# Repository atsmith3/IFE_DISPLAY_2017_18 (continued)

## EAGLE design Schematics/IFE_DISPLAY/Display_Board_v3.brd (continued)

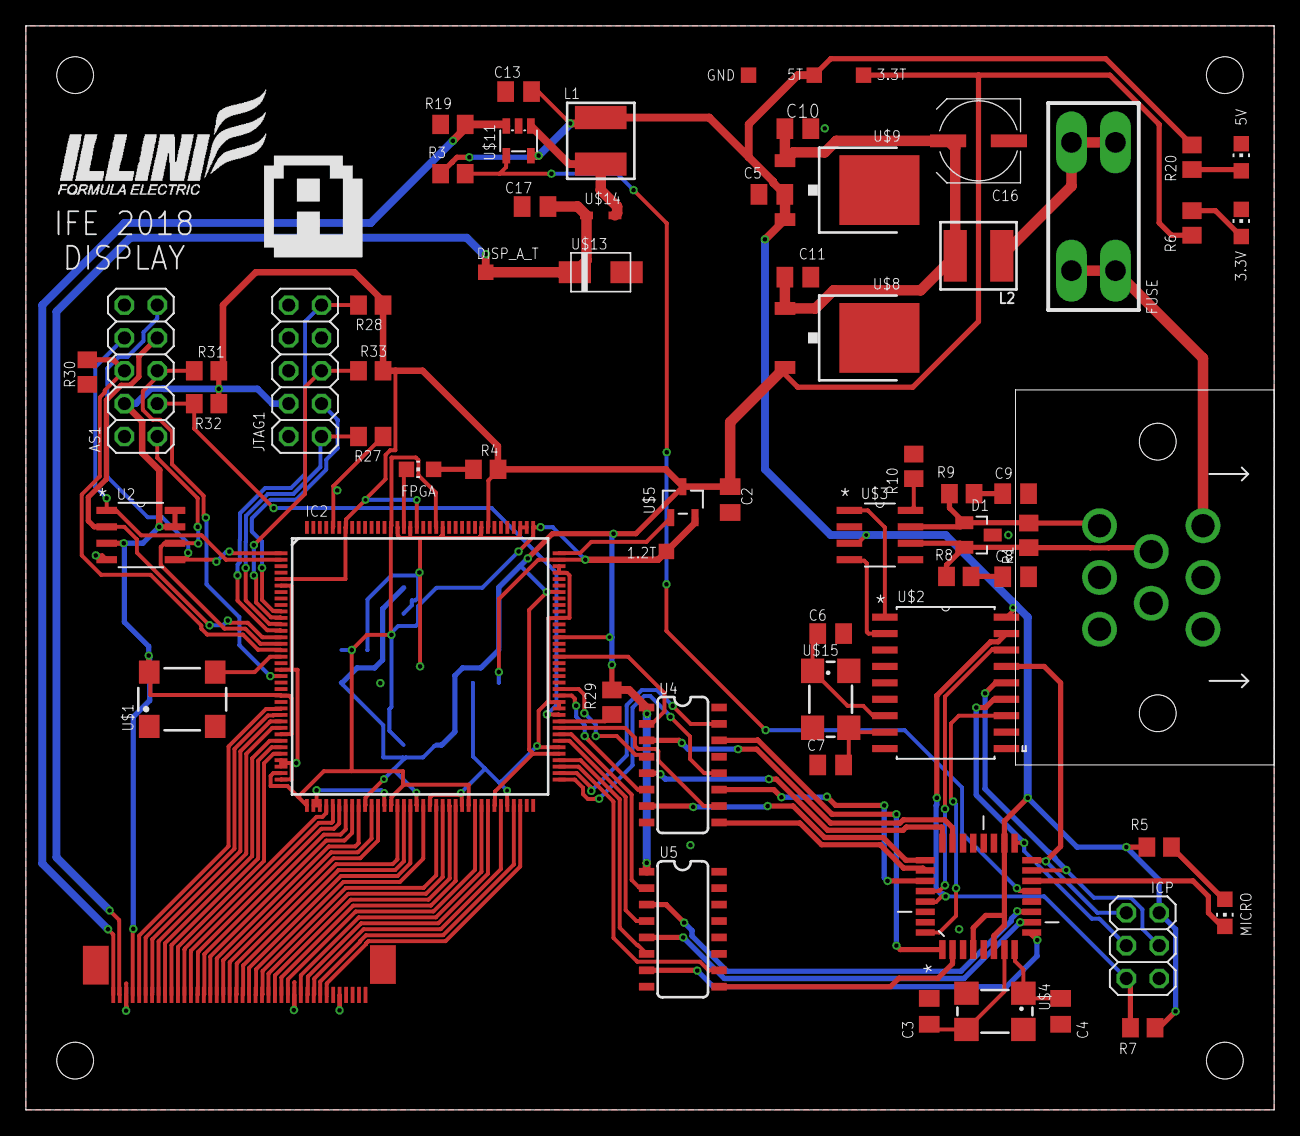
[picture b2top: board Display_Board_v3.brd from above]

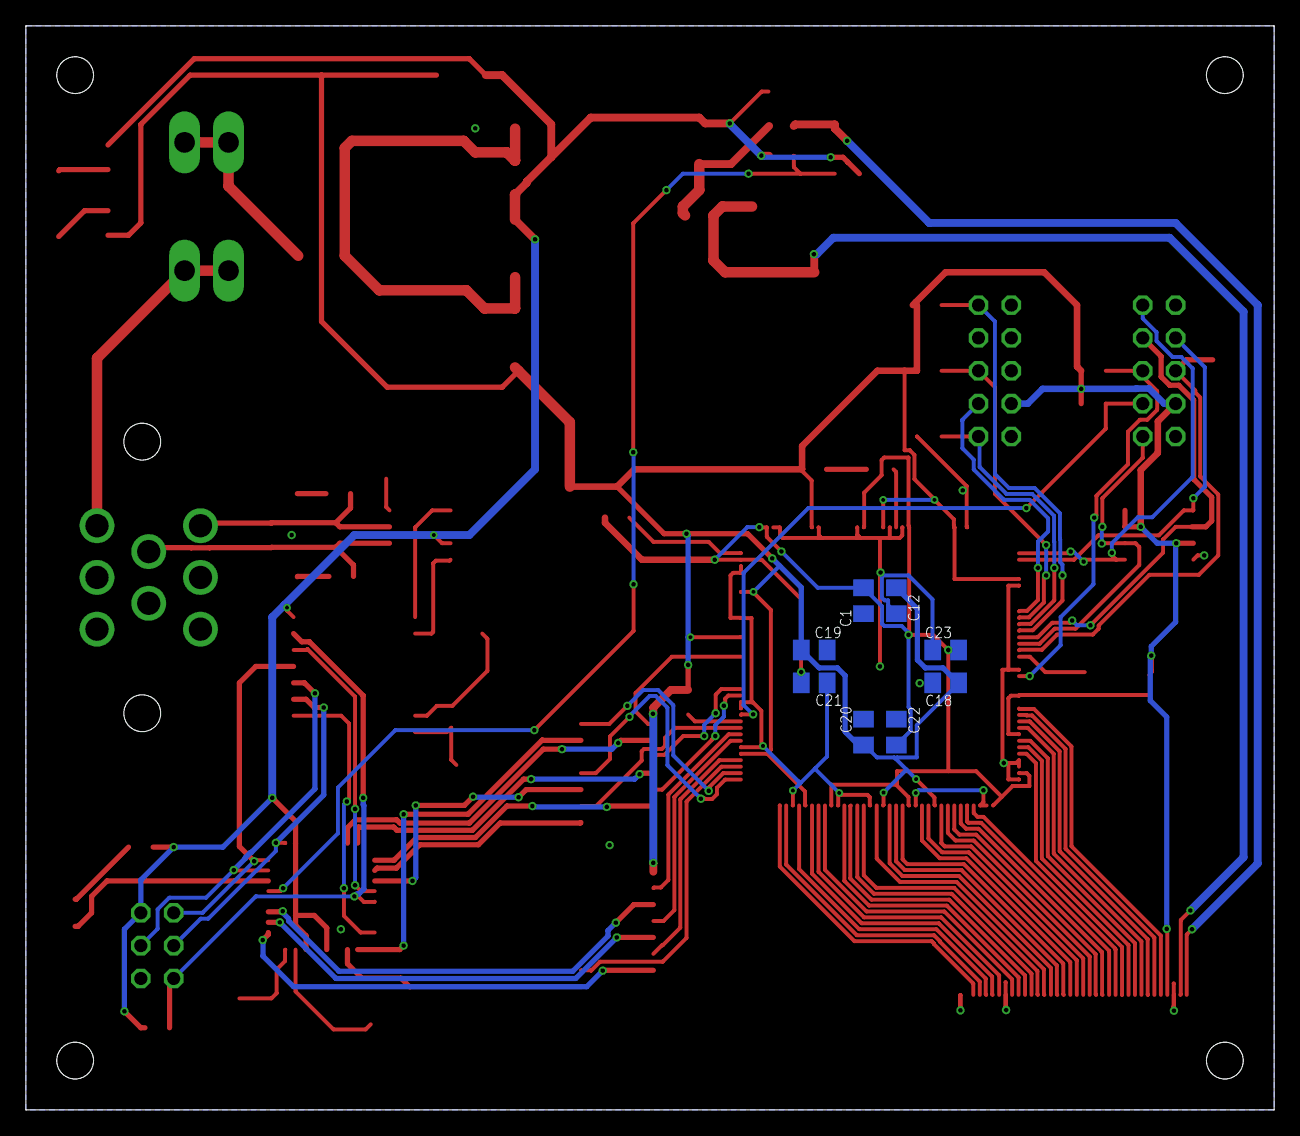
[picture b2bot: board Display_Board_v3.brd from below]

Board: 2 copper layers, 96.5 x 83.8 mm, 73 parts (8 on the bottom side), 96 nets.

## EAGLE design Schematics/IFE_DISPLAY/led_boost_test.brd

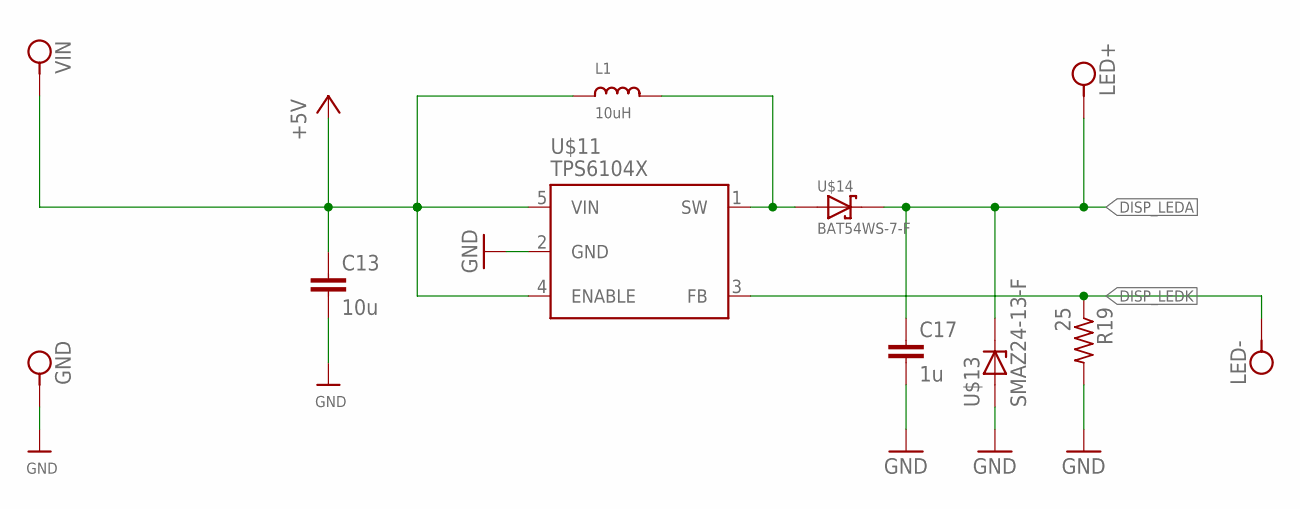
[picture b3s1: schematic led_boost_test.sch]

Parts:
C13: 10u; C0805K
C17: 1u; C0805K
GND: MOTOR_PAD
L1: 10uH; INDUCTOR_5X5MM_NR5040_NOTHERMALS
LED+: MOTOR_PAD
LED-: MOTOR_PAD
R19: 25; R0805
U$11: TPS6104X; SOT23-5L
U$13: SMAZ24-13-F; SMA_DIODE
U$14: BAT54WS-7-F; SOD323
VIN: MOTOR_PAD

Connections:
+5V: C13.1, L1.P$1 (1), U$11.4 (ENABLE), U$11.5 (VIN), VIN.P$1
DISP_LEDA: C17.1, LED+.P$1, U$13.C, U$14.1 (C)
DISP_LEDK: LED-.P$1, R19.1, U$11.3 (FB)
GND: C13.2, C17.2, GND.P$1, R19.2, U$11.2 (GND), U$13.A
unnamed: L1.P$2 (2), U$11.1 (SW), U$14.2 (A)

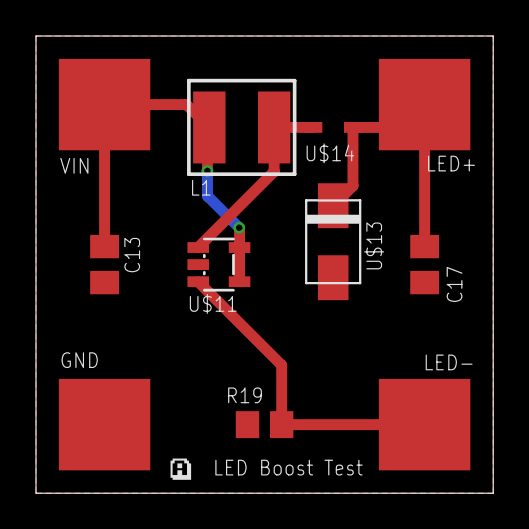
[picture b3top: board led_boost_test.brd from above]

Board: 2 copper layers, 25.4 x 25.4 mm, 11 parts (0 on the bottom side), 5 nets.

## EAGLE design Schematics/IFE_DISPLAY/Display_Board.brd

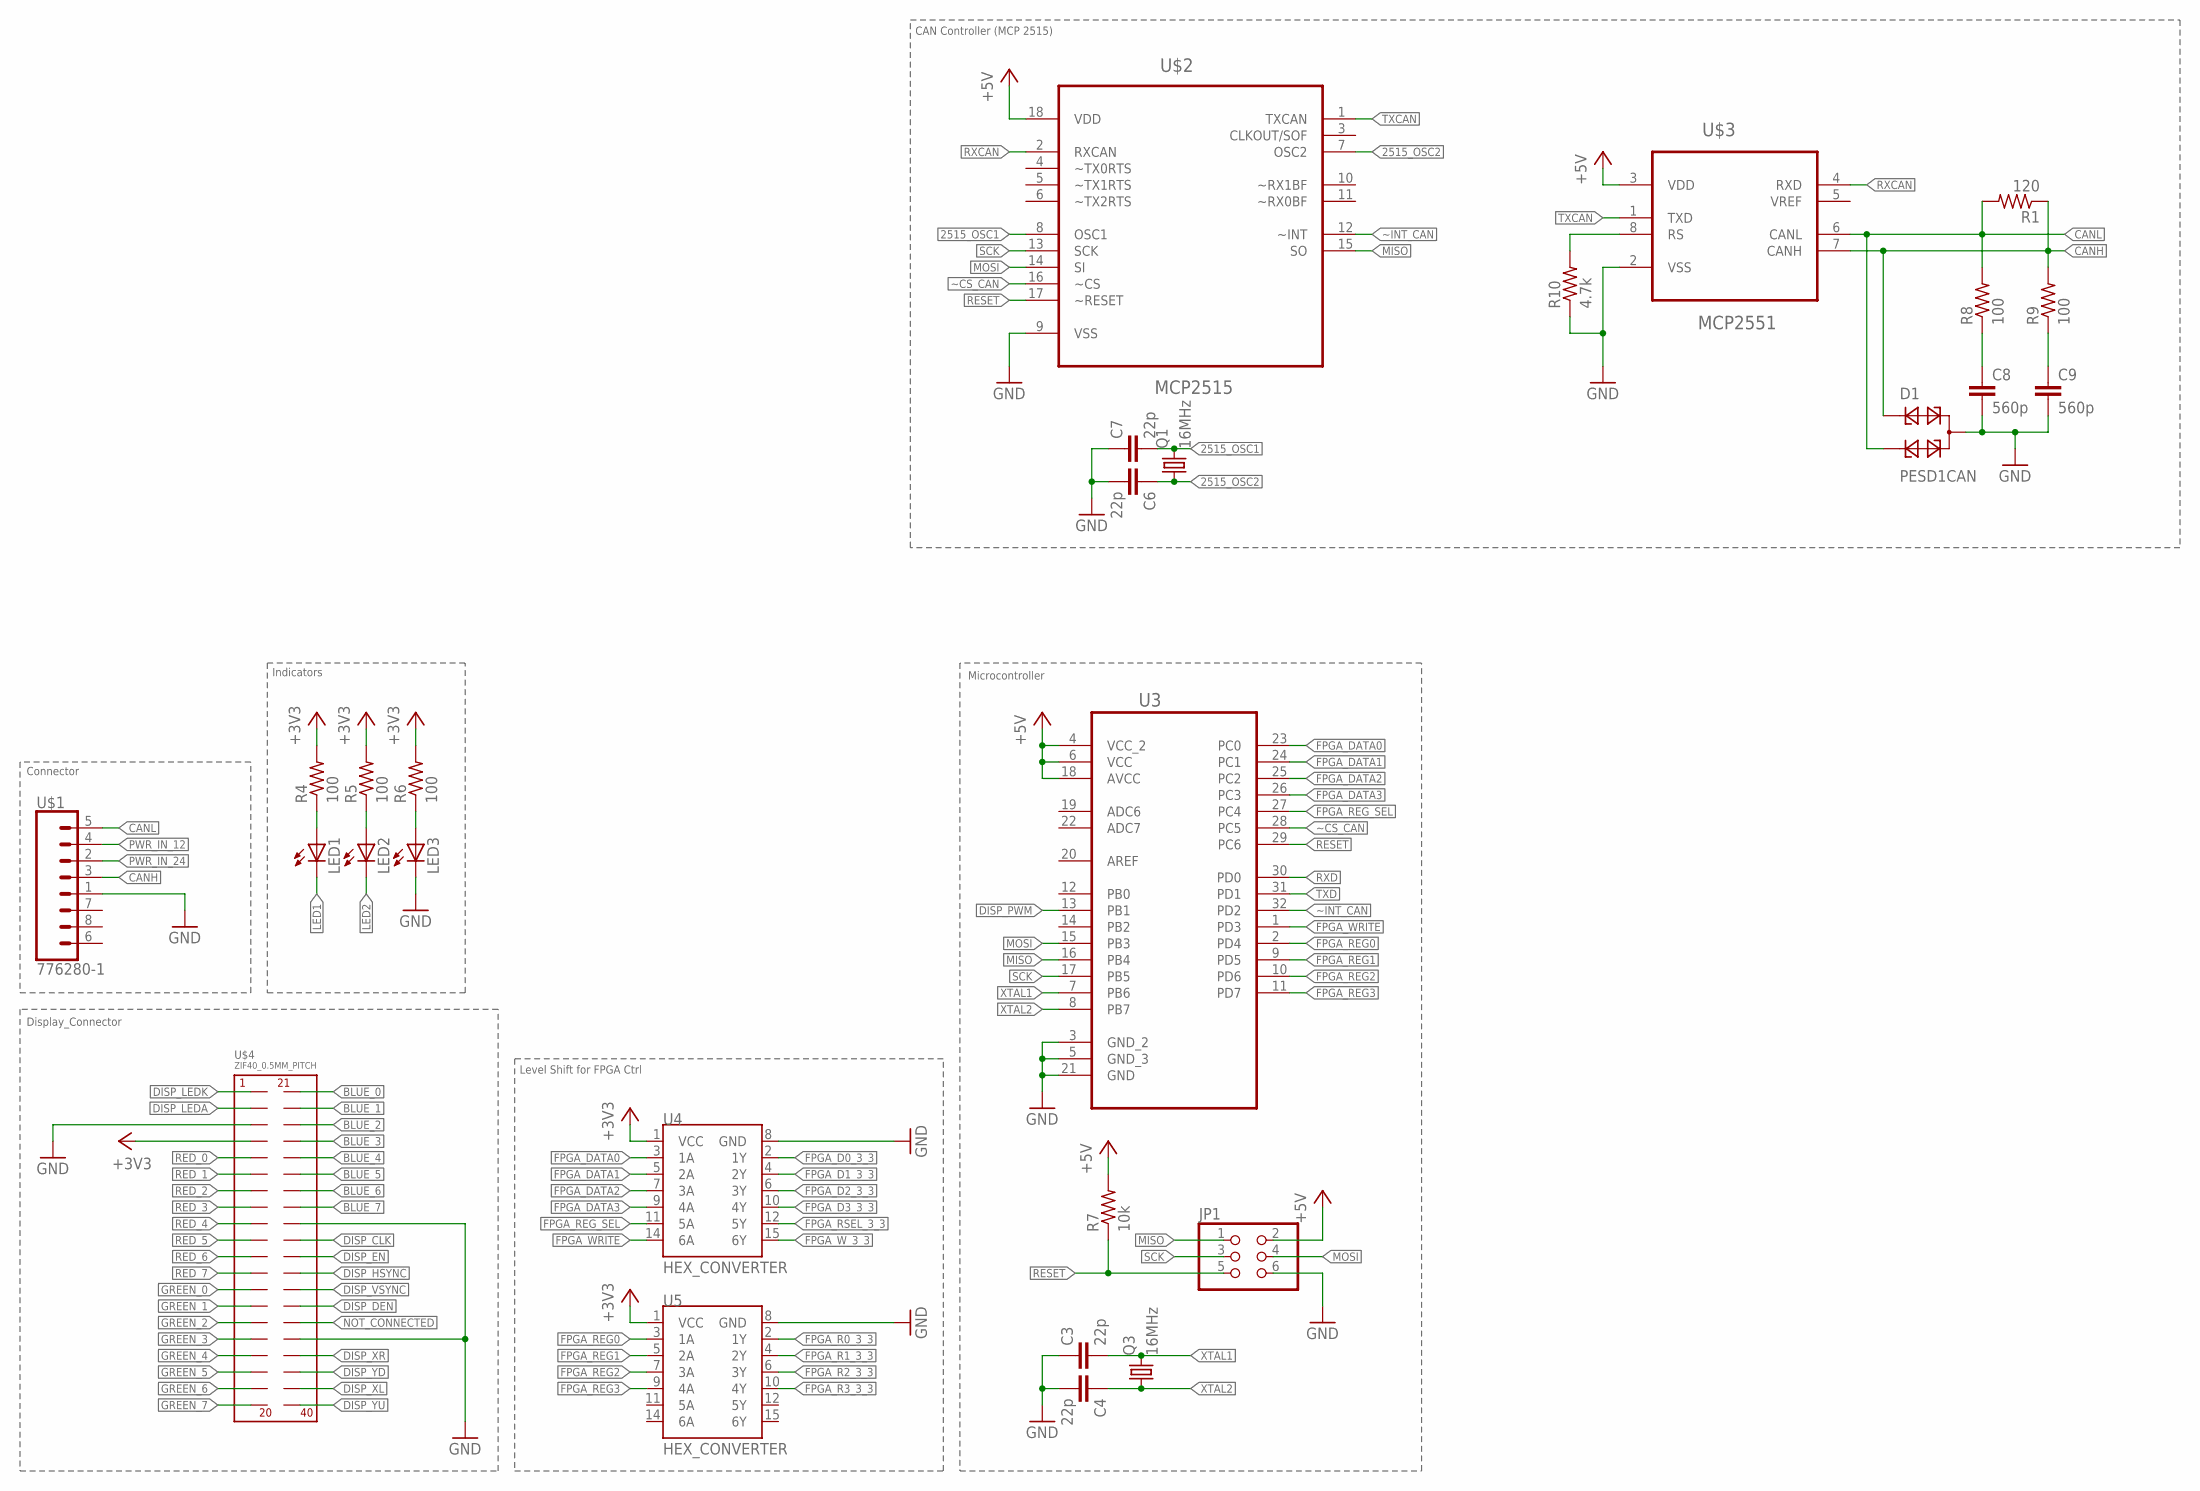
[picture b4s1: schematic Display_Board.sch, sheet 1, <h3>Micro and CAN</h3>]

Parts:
C3, C4, C6, C7: 22p; C0805K
C8, C9: 560p; C0805K
D1: PESD1CAN; SOT23
JP1: PINHD-2X3; 2X03
LED1, LED2, LED3: LEDCHIP-LED0805; CHIP-LED0805
Q1, Q3: 16MHz; CTS406
R1: 120; R0805
R4, R5, R6, R8, R9: 100; R0805
R7: 10k; R0805
R10: 4.7k; R0805
U3: ATMEGA328P-AU; QFP80P900X900X120-32N
U4, U5: HEX_CONVERTER; SO016
U$1: 776280-1
U$2: MCP2515; SOIC127P1034X264-18N
U$3: MCP2551; SOIC127P600X175-8N
U$4: ZIF40_0.5MM_PITCH; ZIF40

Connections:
2515_OSC1: C7.2, Q1.3 (2), U$2.8 (OSC1)
2515_OSC2: C6.1, Q1.1, U$2.7 (OSC2)
+3V3: R4.2, R5.2, R6.2, U4.1 (VCC), U5.1 (VCC), U$4.P$4; also elsewhere on the board
+5V: JP1.2, R7.2, U3.4 (VCC_2), U3.6 (VCC), U3.18 (AVCC), U$2.18 (VDD), U$3.3 (VDD); also elsewhere on the board
BLUE_0: U$4.P$21; also elsewhere on the board
BLUE_1: U$4.P$22; also elsewhere on the board
BLUE_2: U$4.P$23; also elsewhere on the board
BLUE_3: U$4.P$24; also elsewhere on the board
BLUE_4: U$4.P$25; also elsewhere on the board
BLUE_5: U$4.P$26; also elsewhere on the board
BLUE_6: U$4.P$27; also elsewhere on the board
BLUE_7: U$4.P$28; also elsewhere on the board
CANH: D1.1, R1.1, R9.2, U$1.3 (5), U$3.7 (CANH)
CANL: D1.2, R1.2, R8.2, U$1.5 (8), U$3.6 (CANL)
DISP_CLK: U$4.P$30; also elsewhere on the board
DISP_DEN: U$4.P$34; also elsewhere on the board
DISP_EN: U$4.P$31; also elsewhere on the board
DISP_HSYNC: U$4.P$32; also elsewhere on the board
DISP_LEDA: U$4.P$2; also elsewhere on the board
DISP_LEDK: U$4.P$1; also elsewhere on the board
DISP_PWM: U3.13 (PB1); also elsewhere on the board
DISP_VSYNC: U$4.P$33; also elsewhere on the board
DISP_XL: U$4.P$39
DISP_XR: U$4.P$37
DISP_YD: U$4.P$38
DISP_YU: U$4.P$40
FPGA_D0_3_3: U4.2 (1Y); also elsewhere on the board
FPGA_D1_3_3: U4.4 (2Y); also elsewhere on the board
FPGA_D2_3_3: U4.6 (3Y); also elsewhere on the board
FPGA_D3_3_3: U4.10 (4Y); also elsewhere on the board
FPGA_DATA0: U3.23 (PC0), U4.3 (1A)
FPGA_DATA1: U3.24 (PC1), U4.5 (2A)
FPGA_DATA2: U3.25 (PC2), U4.7 (3A)
FPGA_DATA3: U3.26 (PC3), U4.9 (4A)
FPGA_R0_3_3: U5.2 (1Y); also elsewhere on the board
FPGA_R1_3_3: U5.4 (2Y); also elsewhere on the board
FPGA_R2_3_3: U5.6 (3Y); also elsewhere on the board
FPGA_R3_3_3: U5.10 (4Y); also elsewhere on the board
FPGA_REG0: U3.2 (PD4), U5.3 (1A)
FPGA_REG1: U3.9 (PD5), U5.5 (2A)
FPGA_REG2: U3.10 (PD6), U5.7 (3A)
FPGA_REG3: U3.11 (PD7), U5.9 (4A)
FPGA_REG_SEL: U3.27 (PC4), U4.11 (5A)
FPGA_RSEL_3_3: U4.12 (5Y); also elsewhere on the board
FPGA_WRITE: U3.1 (PD3), U4.14 (6A)
FPGA_W_3_3: U4.15 (6Y); also elsewhere on the board
GND: C3.1, C4.2, C6.2, C7.1, C8.2, C9.2, D1.3, JP1.6, LED3.C, R10.1, U3.3 (GND_2), U3.5 (GND_3), U3.21 (GND), U4.8 (GND), U5.8 (GND), U$1.1 (4), U$2.9 (VSS), U$3.2 (VSS), U$4.P$3, U$4.P$29, U$4.P$36; also elsewhere on the board
GREEN_0: U$4.P$13; also elsewhere on the board
GREEN_1: U$4.P$14; also elsewhere on the board
GREEN_2: U$4.P$15; also elsewhere on the board
GREEN_3: U$4.P$16; also elsewhere on the board
GREEN_4: U$4.P$17; also elsewhere on the board
GREEN_5: U$4.P$18; also elsewhere on the board
GREEN_6: U$4.P$19; also elsewhere on the board
GREEN_7: U$4.P$20; also elsewhere on the board
LED1: LED1.C; also elsewhere on the board
LED2: LED2.C; also elsewhere on the board
MISO: JP1.1, U3.16 (PB4), U$2.15 (SO)
MOSI: JP1.4, U3.15 (PB3), U$2.14 (SI)
unnamed: LED1.A, R4.1
unnamed: LED2.A, R5.1
unnamed: LED3.A, R6.1
unnamed: R10.2, U$3.8 (RS)
unnamed: C8.1, R8.1
unnamed: C9.1, R9.1
NOT_CONNECTED: U$4.P$35
PWR_IN_12: U$1.4 (7); also elsewhere on the board
PWR_IN_24: U$1.2 (6)
RED_0: U$4.P$5; also elsewhere on the board
RED_1: U$4.P$6; also elsewhere on the board
RED_2: U$4.P$7; also elsewhere on the board
RED_3: U$4.P$8; also elsewhere on the board
RED_4: U$4.P$9; also elsewhere on the board
RED_5: U$4.P$10; also elsewhere on the board
RED_6: U$4.P$11; also elsewhere on the board
RED_7: U$4.P$12; also elsewhere on the board
RESET: JP1.5, R7.1, U3.29 (PC6), U$2.17 (~RESET)
RXCAN: U$2.2 (RXCAN), U$3.4 (RXD)
RXD: U3.30 (PD0)
SCK: JP1.3, U3.17 (PB5), U$2.13 (SCK)
TXCAN: U$2.1 (TXCAN), U$3.1 (TXD)
TXD: U3.31 (PD1)
XTAL1: C3.2, Q3.3 (2), U3.7 (PB6)
XTAL2: C4.1, Q3.1, U3.8 (PB7)
~CS_CAN: U3.28 (PC5), U$2.16 (~CS)
~INT_CAN: U3.32 (PD2), U$2.12 (~INT)

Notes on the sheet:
Microcontroller
CAN Controller (MCP 2515)
Indicators
Level Shift for FPGA Ctrl
Connector
Display_Connector

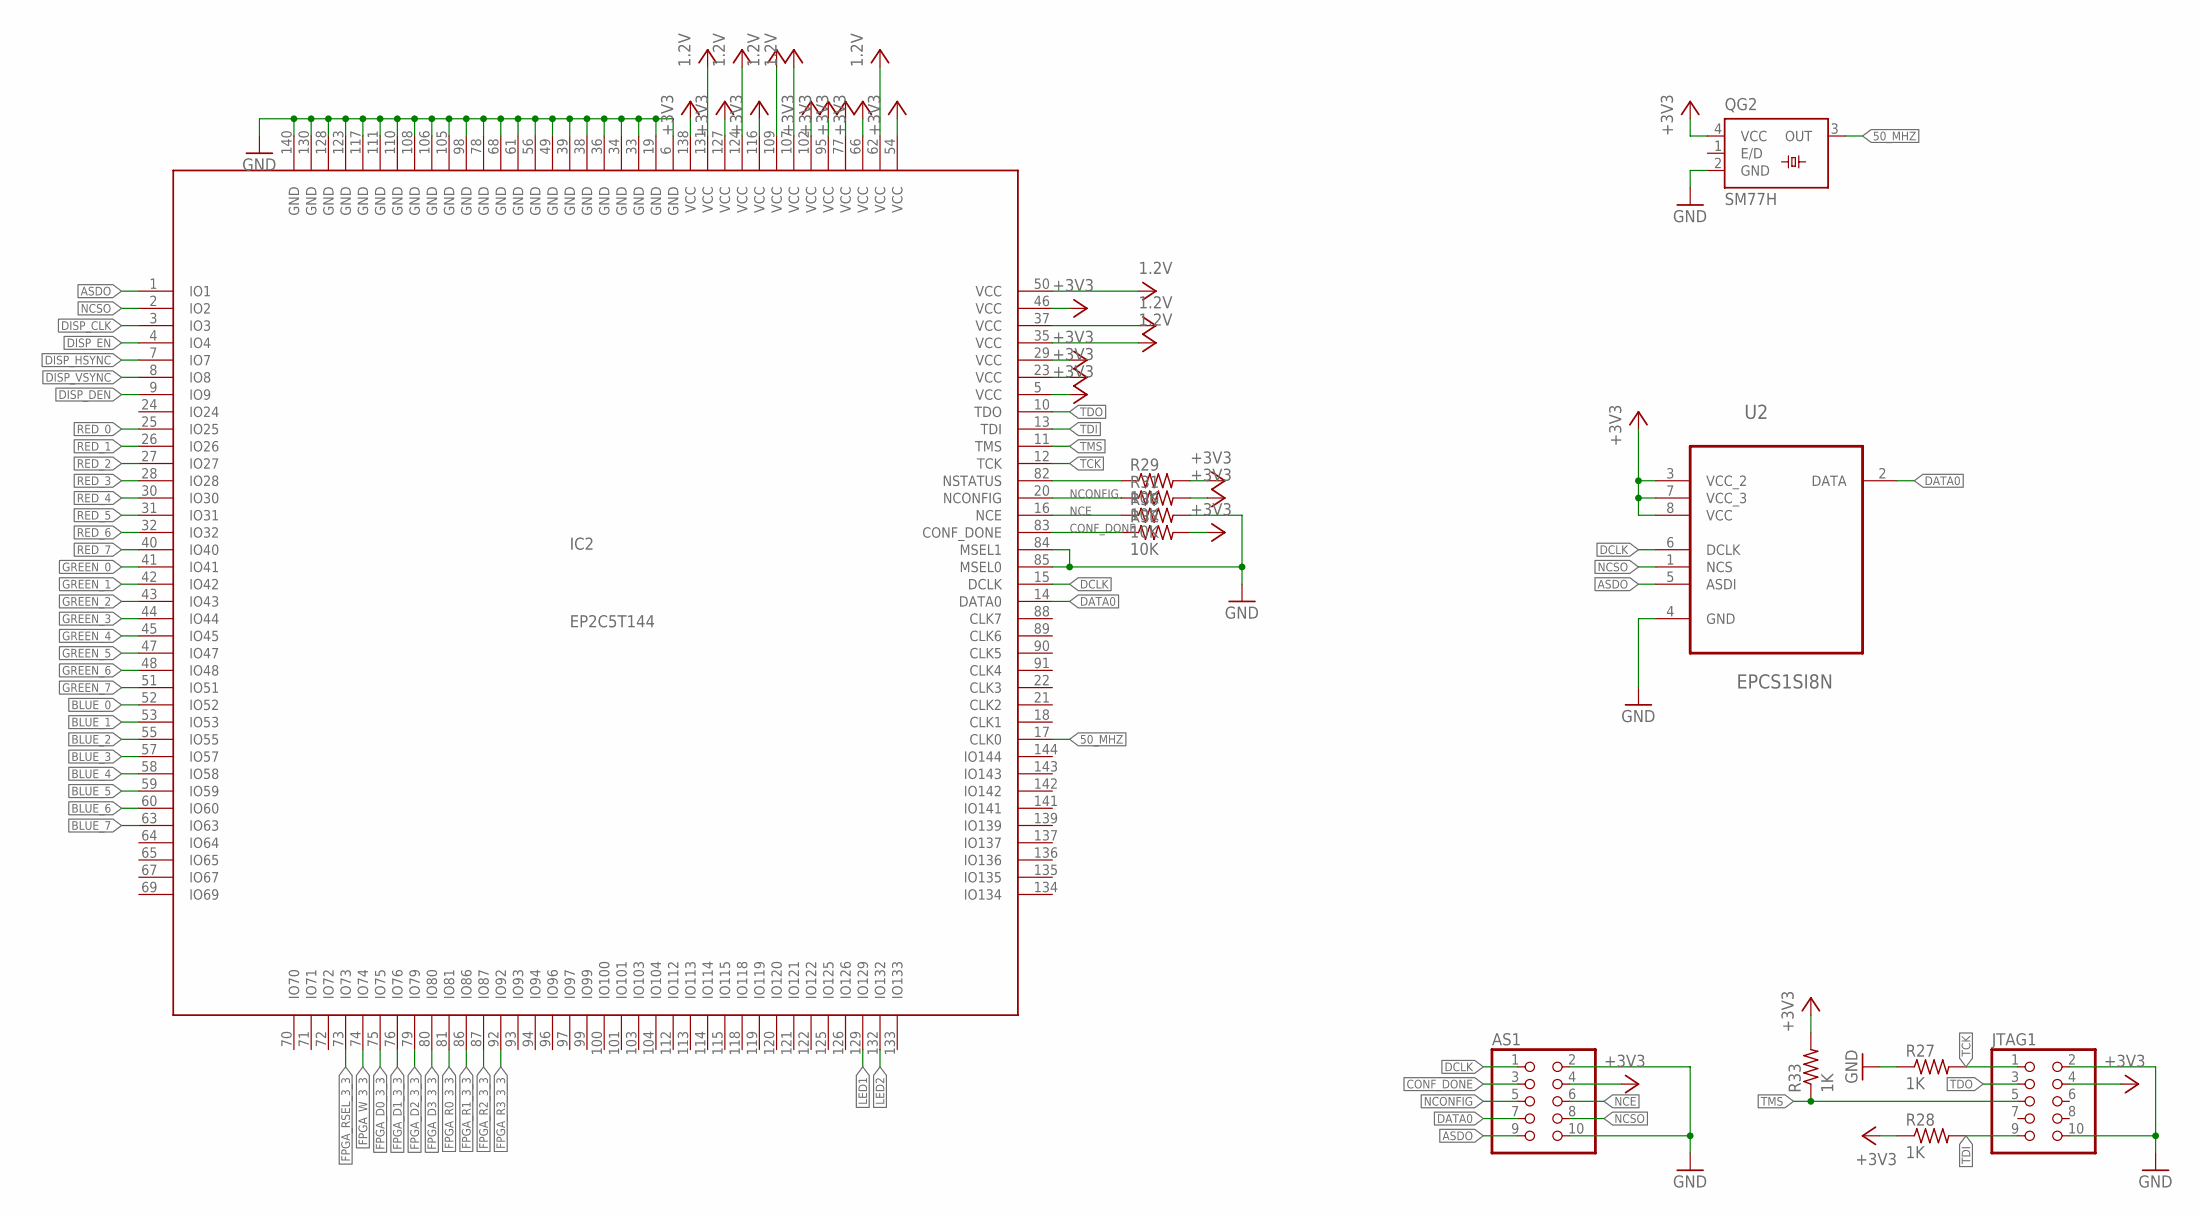
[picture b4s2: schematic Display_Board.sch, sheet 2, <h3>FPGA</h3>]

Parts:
AS1: PINHD-2X5; 2X05
IC2: EP2C5T144; TQFP144
JTAG1: PINHD-2X5; 2X05
QG2: SM77H
R27, R28, R33: 1K; R0805
R29, R30, R31, R32: 10K; R0805
U2: EPCS1SI8N; SOIC127P600X175-8N

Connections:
50_MHZ: IC2.17 (CLK0), QG2.3 (OUT)
+3V3: AS1.4, IC2.5 (VCC), IC2.23 (VCC), IC2.29 (VCC), IC2.46 (VCC), IC2.54 (VCC), IC2.66 (VCC), IC2.77 (VCC), IC2.95 (VCC), IC2.102 (VCC), IC2.116 (VCC), IC2.127 (VCC), IC2.138 (VCC), JTAG1.4, QG2.4 (VCC), R28.1, R29.2, R31.2, R32.2, R33.2, U2.3 (VCC_2), U2.7 (VCC_3), U2.8 (VCC); also elsewhere on the board
ASDO: AS1.9, IC2.1 (IO1), U2.5 (ASDI)
BLUE_0: IC2.52 (IO52); also elsewhere on the board
BLUE_1: IC2.53 (IO53); also elsewhere on the board
BLUE_2: IC2.55 (IO55); also elsewhere on the board
BLUE_3: IC2.57 (IO57); also elsewhere on the board
BLUE_4: IC2.58 (IO58); also elsewhere on the board
BLUE_5: IC2.59 (IO59); also elsewhere on the board
BLUE_6: IC2.60 (IO60); also elsewhere on the board
BLUE_7: IC2.63 (IO63); also elsewhere on the board
CONF_DONE: AS1.3, IC2.83 (CONF_DONE), R32.1
DATA0: AS1.7, IC2.14 (DATA0), U2.2 (DATA)
DCLK: AS1.1, IC2.15 (DCLK), U2.6 (DCLK)
DISP_CLK: IC2.3 (IO3); also elsewhere on the board
DISP_DEN: IC2.9 (IO9); also elsewhere on the board
DISP_EN: IC2.4 (IO4); also elsewhere on the board
DISP_HSYNC: IC2.7 (IO7); also elsewhere on the board
DISP_VSYNC: IC2.8 (IO8); also elsewhere on the board
FPGA_D0_3_3: IC2.75 (IO75); also elsewhere on the board
FPGA_D1_3_3: IC2.76 (IO76); also elsewhere on the board
FPGA_D2_3_3: IC2.79 (IO79); also elsewhere on the board
FPGA_D3_3_3: IC2.80 (IO80); also elsewhere on the board
FPGA_R0_3_3: IC2.81 (IO81); also elsewhere on the board
FPGA_R1_3_3: IC2.86 (IO86); also elsewhere on the board
FPGA_R2_3_3: IC2.87 (IO87); also elsewhere on the board
FPGA_R3_3_3: IC2.92 (IO92); also elsewhere on the board
FPGA_RSEL_3_3: IC2.73 (IO73); also elsewhere on the board
FPGA_W_3_3: IC2.74 (IO74); also elsewhere on the board
GND: AS1.2, AS1.10, IC2.6 (GND), IC2.19 (GND), IC2.33 (GND), IC2.34 (GND), IC2.36 (GND), IC2.38 (GND), IC2.39 (GND), IC2.49 (GND), IC2.56 (GND), IC2.61 (GND), IC2.68 (GND), IC2.78 (GND), IC2.84 (MSEL1), IC2.85 (MSEL0), IC2.98 (GND), IC2.105 (GND), IC2.106 (GND), IC2.108 (GND), IC2.110 (GND), IC2.111 (GND), IC2.117 (GND), IC2.123 (GND), IC2.128 (GND), IC2.130 (GND), IC2.140 (GND), JTAG1.2, JTAG1.10, QG2.2 (GND), R27.1, R30.2, U2.4 (GND); also elsewhere on the board
GREEN_0: IC2.41 (IO41); also elsewhere on the board
GREEN_1: IC2.42 (IO42); also elsewhere on the board
GREEN_2: IC2.43 (IO43); also elsewhere on the board
GREEN_3: IC2.44 (IO44); also elsewhere on the board
GREEN_4: IC2.45 (IO45); also elsewhere on the board
GREEN_5: IC2.47 (IO47); also elsewhere on the board
GREEN_6: IC2.48 (IO48); also elsewhere on the board
GREEN_7: IC2.51 (IO51); also elsewhere on the board
LED1: IC2.129 (IO129); also elsewhere on the board
LED2: IC2.132 (IO132); also elsewhere on the board
unnamed: IC2.82 (NSTATUS), R29.1
NCE: AS1.6, IC2.16 (NCE), R30.1
NCONFIG: AS1.5, IC2.20 (NCONFIG), R31.1
NCSO: AS1.8, IC2.2 (IO2), U2.1 (NCS)
RED_0: IC2.25 (IO25); also elsewhere on the board
RED_1: IC2.26 (IO26); also elsewhere on the board
RED_2: IC2.27 (IO27); also elsewhere on the board
RED_3: IC2.28 (IO28); also elsewhere on the board
RED_4: IC2.30 (IO30); also elsewhere on the board
RED_5: IC2.31 (IO31); also elsewhere on the board
RED_6: IC2.32 (IO32); also elsewhere on the board
RED_7: IC2.40 (IO40); also elsewhere on the board
TCK: IC2.12 (TCK), JTAG1.1, R27.2
TDI: IC2.13 (TDI), JTAG1.9, R28.2
TDO: IC2.10 (TDO), JTAG1.3
TMS: IC2.11 (TMS), JTAG1.5, R33.1
VCC: IC2.35 (VCC), IC2.37 (VCC), IC2.50 (VCC), IC2.62 (VCC), IC2.107 (VCC), IC2.109 (VCC), IC2.124 (VCC), IC2.131 (VCC); also elsewhere on the board

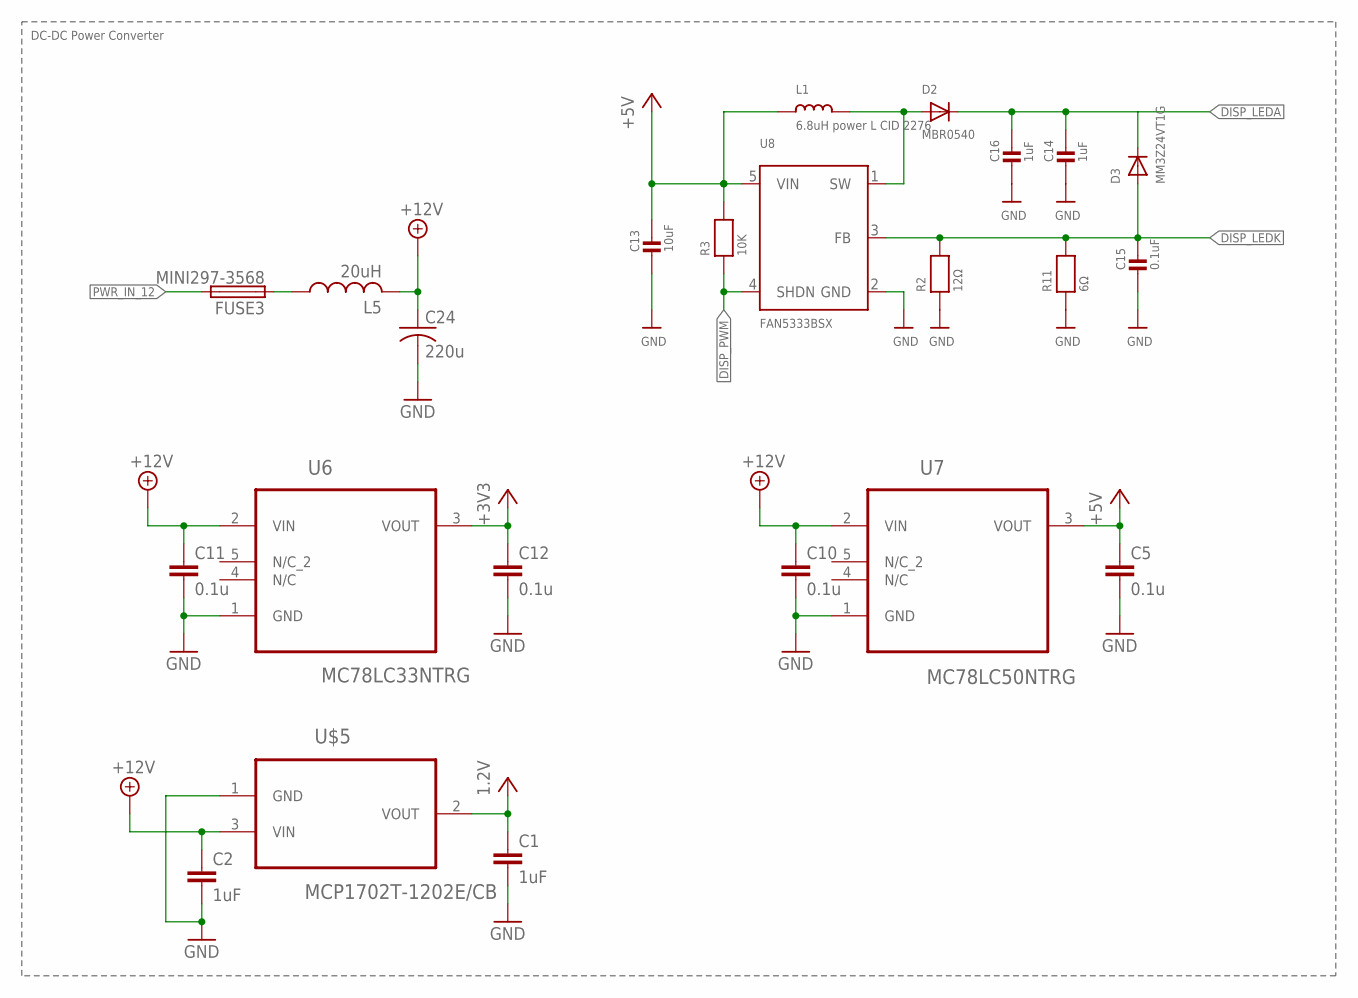
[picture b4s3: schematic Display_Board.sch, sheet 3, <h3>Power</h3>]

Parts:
C1, C2: 1uF; C0805K
C5, C10, C11, C12: 0.1u; C0805K
C13: 10uF; _0805MP
C14, C16: 1uF; _0805MP
C15: 0.1uF; _0805MP
C24: 220u; C1206
D2: MBR0540; SOD-123
D3: MM3Z24VT1G; SMADIODE
FUSE3: MINI297-3568; 3568
L1: 6.8uH power L CID 2276; INDUCTOR_5X5MM_NR5040_NOTHERMALS
L5: 20uH; MSS7348
R2: 12Ω; _0805MP
R3: 10K; _0805MP
R11: 6Ω; _0805MP
U6: MC78LC33NTRG; SOT95P275X110-5N
U7: MC78LC50NTRG; SOT95P275X110-5N
U8: FAN5333BSX; SOT23-5@1
U$5: MCP1702T-1202E/CB; SOT95P300X145-3N

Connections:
+3V3: C12.1, U6.3 (VOUT); also elsewhere on the board
+5V: C5.1, C13.1, L1.P$1 (1), R3.2, U7.3 (VOUT), U8.5 (VIN); also elsewhere on the board
+12V: C2.1, C10.1, C11.1, C24.1, L5.P$2 (2), U6.2 (VIN), U7.2 (VIN), U$5.3 (VIN)
DISP_LEDA: C14.1, C16.1, D2.C, D3.C; also elsewhere on the board
DISP_LEDK: C15.1, D3.A, R2.2, R11.2, U8.3 (FB); also elsewhere on the board
DISP_PWM: R3.1, U8.4 (SHDN); also elsewhere on the board
GND: C1.2, C2.2, C5.2, C10.2, C11.2, C12.2, C13.2, C14.2, C15.2, C16.2, C24.2, R2.1, R11.1, U6.1 (GND), U7.1 (GND), U8.2 (GND), U$5.1 (GND); also elsewhere on the board
unnamed: FUSE3.P$1 (1), FUSE3.P$4 (1), L5.P$1 (1)
unnamed: D2.A, L1.P$2 (2), U8.1 (SW)
PWR_IN_12: FUSE3.P$2 (2), FUSE3.P$3 (2); also elsewhere on the board
VCC: C1.1, U$5.2 (VOUT); also elsewhere on the board

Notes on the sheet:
DC-DC Power Converter

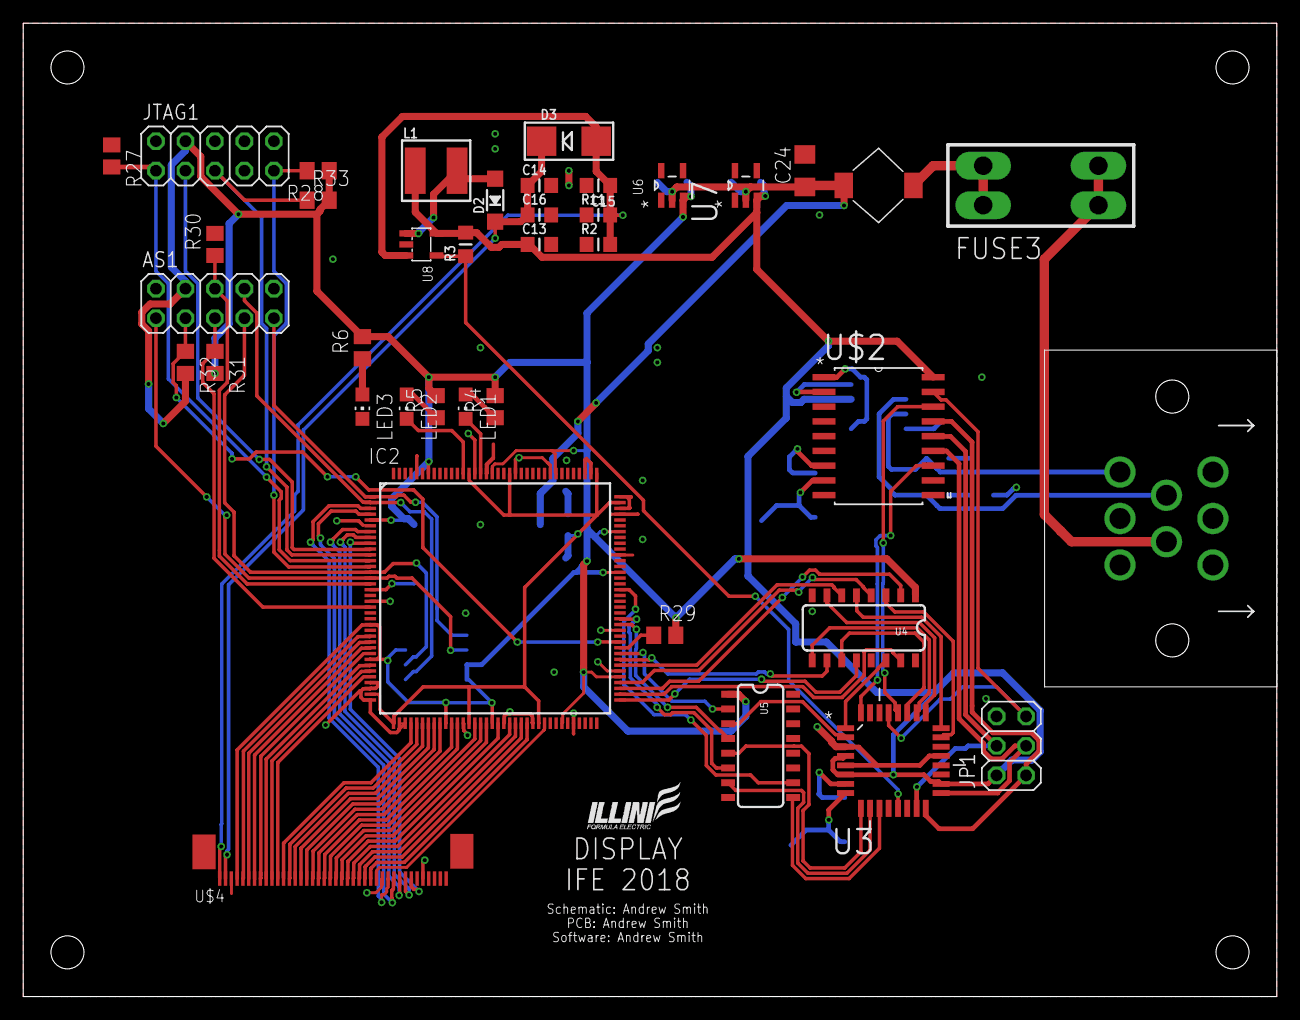
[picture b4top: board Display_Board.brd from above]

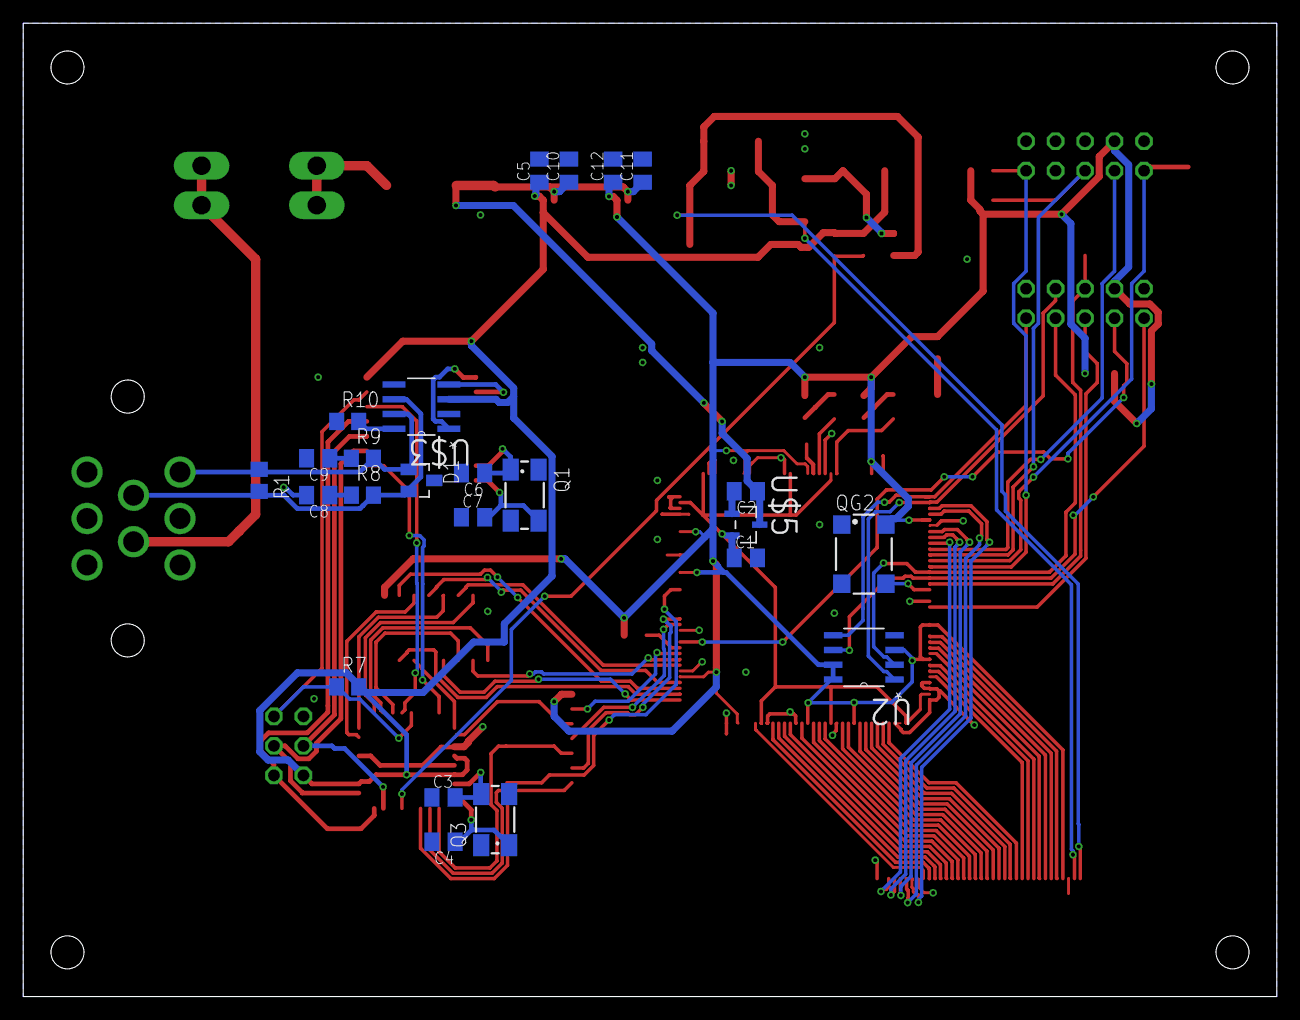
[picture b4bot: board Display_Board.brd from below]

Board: 2 copper layers, 108.0 x 83.8 mm, 63 parts (24 on the bottom side), 95 nets.

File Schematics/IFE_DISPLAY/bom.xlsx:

Part | Value | Device | Package | Description | MPN | Quantity | Price | Link
R11 | 6 | RESISTOR_0805MP | _0805MP | Resistors |  | 1
R2 | 12 | RESISTOR_0805MP | _0805MP | Resistors |  | 1
AS1 |  | PINHD-2X5 | 2X05 | PIN HEADER |  | 1
JP1 |  | PINHD-2X3 | 2X03 | PIN HEADER |  | 1
JTAG1 |  | PINHD-2X5 | 2X05 | PIN HEADER |  | 1
LED1 |  | LEDCHIP-LED0805 | CHIP-LED0805 | LED |  | 3
U3 |  | ATMEGA328P-AU | QFP80P900X900X120-32N | 8-bit Microcontroller with In-System Programmable Flash | ATMEGA328P-AU | 1 | 2.1800000000000002 | https://www.digikey.com/product-detail/en/microchip-technolo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
C5 | 0.1u | C-EUC0805K | C0805K | CAPACITOR, European symbol |  | 5
R4 | 100 | R-US_R0805 | R0805 | RESISTOR, American symbol |  | 5
R3 | 10K | RESISTOR_0805MP | _0805MP | Resistors |  | 6
C13 | 10uF | CAP_CERAMIC_0805MP | _0805MP | Ceramic Capacitors |  | 1
R1 | 120 | R-US_R0805 | R0805 | RESISTOR, American symbol |  | 1
Q1 | 16MHz | CRYSTALCTS406 | CTS406 | CRYSTAL |  | 2
R27 | 1K | R-US_R0805 | R0805 | RESISTOR, American symbol |  | 3
C1 | 1uF | C-EUC0805K | C0805K | CAPACITOR, European symbol |  | 4
L5 | 20uH | MSS7348 | MSS7348 | Inductors |  | 1
C24 | 220u | C1206 | C1206 |  |  | 1
C3 | 22p | C-EUC0805K | C0805K | CAPACITOR, European symbol |  | 4
R10 | 4.7k | R-US_R0805 | R0805 | RESISTOR, American symbol |  | 1
C8 | 560p | C-EUC0805K | C0805K | CAPACITOR, European symbol |  | 2
L1 | 6.8uH power L CID 2276 | INDUCTORNR5040 | INDUCTOR_5X5MM_NR5040_NOTHERMALS | Inductors |  | 1
U$1 | 776280-1 | 776280-1 | 776280-1 | AMPSEAL 8pin Connector |  | 1
IC2 | EP2C5T144 | EP2C5T144 | TQFP144 | EP2C5T144 | EP2C5T144C8N | 1 | 14.72 | https://www.digikey.com/product-detail/en/altera/EP2C5T144C8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
U2 | EPCS1SI8N | EPCS1SI8N | SOIC127P600X175-8N | Serial Configuration Devices | EPCS1SI8N | 1 | 4.2699999999999996 | https://www.digikey.com/products/en?keywords=EPCS1SI8N
U8 | FAN5333BSX | FAN5331 | SOT23-5@1 | FAN5331 - LED/OLED 20V Boost Converter |  | 1 | 0.99 | https://www.digikey.com/product-detail/en/on-semiconductor/F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
U4 | HEX_CONVERTER | HEX_CONVERTER | SO016 | 74HC4050 Hex Buffer Level Shifter SMD SO016 |  | 2 | 0.47 | https://www.digikey.com/product-detail/en/nexperia-usa-inc/7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
D2 | MBR0540 | DIODESOD-123 | SOD-123 | Diode |  | 1 | 0.41 | https://www.digikey.com/product-detail/en/micro-commercial-c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
U6 | MC78LC33NTRG | MC78LC33NTRG | SOT95P275X110-5N | Micropower Voltage Regulator | MC78LC33NTRG | 1 | 0.91 | https://www.digikey.com/product-detail/en/on-semiconductor/M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
U7 | MC78LC50NTRG | MC78LC50NTRG | SOT95P275X110-5N | Micropower Voltage Regulator | MC78LC50NTRG | 1 | 0.82 | https://www.digikey.com/product-detail/en/on-semiconductor/M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
U$5 | MCP1702T-1202E/CB | MCP1702T-1802E/CB | SOT95P300X145-3N | Low Quiescent Current LDO Regulator | MCP1702T-1802E/CB | 1 | 0.5 | https://www.digikey.com/product-detail/en/microchip-technolo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
U$2 | MCP2515 | MCP2515-I/SO | SOIC127P1034X264-18N | CAN Controller | MCP2515-I/SO | 1 | 1.91 | https://www.digikey.com/product-detail/en/microchip-technolo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
U$3 | MCP2551 | MCP2551-I/SN | SOIC127P600X175-8N | High-Speed CAN Transceiver | MCP2551-I/SN | 1 | 1.24 | https://www.digikey.com/product-detail/en/microchip-technolo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
FUSE3 | MINI297-3568 | MINI297-3568 | 3568 |  |  | 1
D3 | MM3Z24VT1G | DIODESMA | SMADIODE | Diode |  | 1 | 0.3 | https://www.digikey.com/product-detail/en/on-semiconductor/S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
D1 | PESD1CAN | PESD1CAN | SOT23 | CAN bus ESD protection diode |  | 1 | 0.93 | https://www.digikey.com/product-detail/en/littelfuse-inc/SM7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
QG2 | SM77H | SM77H | SM77H | 3.3V CMOS Clock Oscillator |  | 1 | 1.86 | https://www.digikey.com/product-detail/en/abracon-llc/ASCO-5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
U$4 | ZIF40_0.5MM_PITCH | ZIF40_0.5MM_PITCH | ZIF40 | 40 Pin 0.5mm ptch FPC Connector |  | 1 | 0.9 | https://www.digikey.com/product-detail/en/amphenol-fci/62684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
